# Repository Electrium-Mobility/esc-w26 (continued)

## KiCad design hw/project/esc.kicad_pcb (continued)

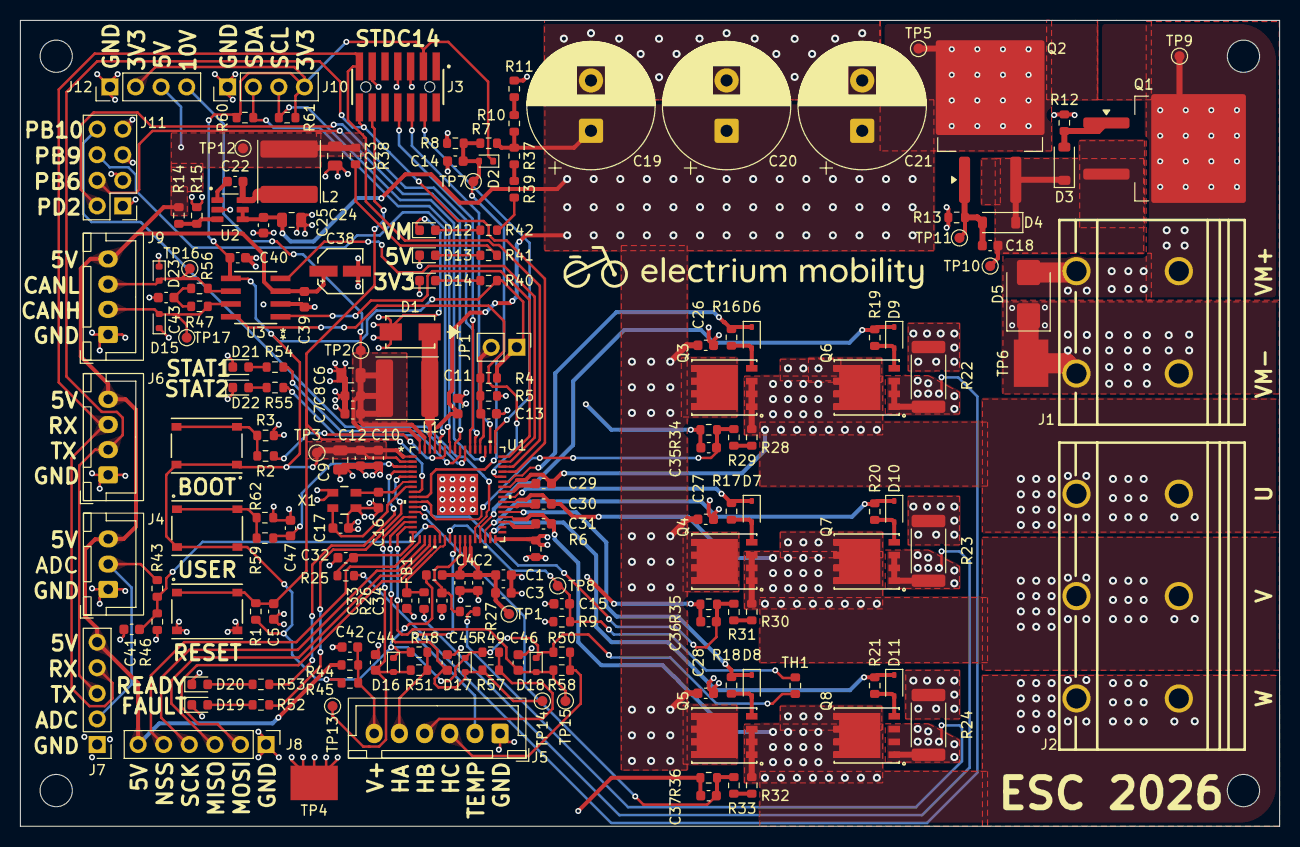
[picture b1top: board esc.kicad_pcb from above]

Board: 4 copper layers, 125.0 x 80.0 mm, 185 parts (0 on the bottom side), 101 nets.

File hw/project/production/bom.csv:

Designator,Footprint,Quantity,Value,LCSC Part #
"C1, C29, C3, C30, C31",0603,5,1uF/50V,C15849
"C10, C12, C14, C15, C2, C22, C25, C39, C4, C40, C41, C42, C47, C5, C7, C8",0603,16,0.1uF,C15725
"C11, C18, C26, C27, C28",0603,5,0.22uF/100V,C2169715
"C13, C32, C33, C34, C43, C44, C45, C46",0603,8,1nF/100V,C113793
"C16, C17",0603,2,8pF,C519117
"C19, C20, C21",CP_Radial_D12.5mm_P5.00mm,3,470uF/80V,C385881
C23,0805,1,22uF/25V,C45783
C24,0805,1,2.2uF/100V,C2981733
"C35, C36, C37",0603,3,470pF/100V,C326973
C38,EEEFKC220UAR,1,22uF/10V,C401733
"C6, C9",0805,2,10uF/50V,C440198
D1,SMA_STM,1,STPS1H100A,C165701
"D10, D11, D6, D7, D8, D9",D_SOD-323,6,BAT48JFILM,C2798199
"D12, D13, D14, D20",0603,4,2Vf_G,C125098
"D15, D23",D_SOD-523,2,5Vwm,C51912417
"D16, D17, D18, D2",D_SOD-523,4,BAT30KFILM,C2926449
D19,0603,1,2Vf_R,C94869
"D21, D22",0603,2,2Vf_A,C5730905
"D3, D4",D_SOD-123,2,12Vz,C699126
D5,D_SMB,1,36.8Vwm,C468909
FB1,0603,1,600@100MHz,C304319
J1,KFA-1016-10_16-2P,1,KFA-1016-10_16-2P,C475110
J10,PinHeader_1x04_P2.54mm_Vertical,1,I2C,C3329732
J11,PinHeader_2x04_P2.54mm_Vertical,1,Misc,C3333874
J12,PinHeader_1x04_P2.54mm_Vertical,1,Voltage Monitor,C3329732
J2,KFA-1016-10_16-3P,1,KFA-1016-10_16-3P,C475111
J3,SAMTEC_FTSH-107-01-L-DV-K-A,1,FTSH-107-01-L-DV-K-A,C5563894
J4,JST_XH_B3B-XH-A_1x03_P2.50mm_Vertical,1,Throttle,C144394
J5,JST_XH_B6B-XH-A_1x06_P2.50mm_Vertical,1,Hall,C144397
J6,JST_XH_B4B-XH-A_1x04_P2.50mm_Vertical,1,Serial,C144395
J7,PinHeader_1x05_P2.54mm_Vertical,1,2.54 Comm,C3347212
J8,PinHeader_1x06_P2.54mm_Vertical,1,SPI,C5427040
J9,JST_XH_B4B-XH-A_1x04_P2.50mm_Vertical,1,CAN,C144395
JP1,PinHeader_1x02_P2.54mm_Vertical,1,DIS_VDSMON,C5426960
L1,L_Sunlord_SWPA6045S,1,18uH,C96954
L2,L_Sunlord_SWPA6045S,1,33uH,C83451
"Q1, Q2",TO-263-2,2,SUM110P06-08L-E3,C5364638
"Q3, Q4, Q5, Q6, Q7, Q8",MOSFET_10N10F7_STM,6,STL110N10F7,C672185
"R1, R2, R3, R43, R46, R48, R49, R5, R50, R51, R57, R58, R59, R62",0603,14,10k,C25804
"R10, R11, R15, R28, R29, R30, R31, R32, R33, R4",0603,10,22.1k,C25961
"R12, R13, R14, R7",0603,4,118k,C25806
"R16, R17, R18, R19, R20, R21, R25, R26, R27",0603,9,10,C22859
"R22, R23, R24",2512,3,1m/3W,C53280154
"R34, R35, R36, R37, R39, R42, R60, R61",0603,8,2.2k,C4190
"R38, R40, R41, R52, R53, R54, R55",0603,7,150,C22808
"R47, R56",0603,2,60.4,C23090
"R6, R44",0603,2,0,C21189
"R8, R9",0603,2,4.7k,C23162
SW1,TS-1187A-B-A-B,1,BOOT0,C318884
SW2,TS-1187A-B-A-B,1,RESET,C318884
SW3,TS-1187A-B-A-B,1,USER,C318884
TH1,0603,1,10k/1%,C440252
TP4,KEYSTONE_5016,1,GND,C238129
TP6,KEYSTONE_5016,1,PGND,C238129
U1,QFN_IN32G4_STM,1,STSPIN32G4,C7434864
U2,LMR51610XDBVR-SOT95P280X145-6N,1,LMR51610XDBVR,C20539658
U3,SOIC8_4P9X3P9MC_MCH,1,ATA6561-GAQW-N,C616016
X1,xtal4_CX3225SB_AVX,1,SWXC5ACVF0-32.000000,C22399832

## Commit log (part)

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2026-01-30 Set up KiCad project with blank hierarchical sheets!
2026-01-30 Set up codebase. Not STM32CubeIDE yet though (when PCB v1 almost done)
2026-01-31 Add template files for Doxygen-style documentation
2026-01-31 Ready to add blank files (I fink)
2026-01-31 Update simulation docs
2026-02-01 Establish some motor/esc config stuff and create first set of functions to implement
2026-02-01 Add contribution steps
2026-02-08 Added esc Setters (throttle_cmd & motor_state) to Public Function Definitions
2026-02-08 Added esc Getters (Faulted, Flags, Inverter) to Public Function Definitions
2026-02-08 Forgot to Save
2026-02-09 Motor Interface / Config - Con/Deconstructors
    ESC initialization, ESC reset, ESC config validity + added preprocessor macros to esc.h subject to change
2026-02-13 Resolving Pull Request Issues
2026-02-13 Feedback Updates
    Improved code readability & removed hardcoding
2026-02-14 added control loop base
2026-02-19 Addressed Styling Choices and added Throttle Max/Min definitions.
2026-02-19 Updating return esc_get_fault_flags types and formatting
2026-02-19 Updated return for esc_is_faulted to != ESC_FAULT_NONE
2026-02-21 buck converter rev_1
2026-02-23 Configuring Control & Output Helpers
    Programmed _esc_update_setpoint, _esc_check_limits, _esc_update_output. Added preprocessor macro MAX_RPM
2026-03-01 Made requested changes
    Added preprocessor macros for deadband values, and fixed blaring fault flag manipulation issues
2026-03-03 fixed minor formatting
2026-03-03 Added Feedback and Commutation Helpers
2026-03-04 Set up Drive schem
2026-03-10 Update sym-lib-table
2026-03-10 fixed according to the comments
2026-03-11 Addressing minor things in PR
2026-03-17 Done with Drive stage EXCEPT analog sensing
2026-03-17 Added STM to Control sheet and proj libs
2026-03-17 Re-organized proj libs
2026-03-18 Cleaned up symbols and added footprint/3d model
2026-03-19 Create hal/ (previously platform/) header files
2026-03-19 Ready to assign hal/ tasks
2026-03-19 Minor edits to KiCad files
2026-03-22 Adding Main MATLAB files to Repo
2026-03-23 Renames & implementation for timing.c adc.c
2026-03-25 Rename timing -> time & cleanup
2026-03-25 pwm.c implementation
    needs revision but mostly complete
2026-03-30 resolving changes
2026-03-30 Pull main in
2026-03-31 Function definitions in host_test_utils.h & pwm.c implementation
2026-03-31 Removed misunderstanding
2026-03-31 input protection schematic and simulations added
2026-03-31 schematic updated
2026-04-01 added the notes as images
2026-04-02 rev_1:Application Circuitry
2026-04-11 host_test_utils.c implementation
2026-06-02 Adjusted notes in schem
2026-06-02 Refactor esc.c
2026-06-02 Further refactor of esc.c
2026-06-05 Adding to base model to sims folder
2026-06-10 Added gpio.c adn fault.c files to hal host
2026-06-13 Bob the builder!
2026-06-13 Fix host state utils bug
2026-06-13 Update docs for building
2026-06-13 Split up commutation method and feedback mechanism
2026-06-13 Clean up docs
2026-06-14 Adding base model to sims folder (#13)
    * Refactor esc.c
    * Further refactor of esc.c
    * Adding to base model to sims folder
    ---------
2026-06-14 Added gpio.c adn fault.c files to hal host (#14)
    * Refactor esc.c
    * Further refactor of esc.c
    * Added gpio.c adn fault.c files to hal host
    ---------
2026-06-14 filled out STSPIN32G4 for application circuitry
2026-06-17 analog sensing
    3 possible options for opamps, bootstrap caps depend on mosfets, so i gave the formula for that in the kicad.
2026-06-23 Revise Arnav's sensing task--changes to be made
2026-06-24 Upgrade to Kicad 10!
2026-06-25 Replace drive sheet with latest
2026-06-26 Updated local/hierarchical labels, renamed signals, and added alternate pin functions. Still need to review application circuit values fr.
2026-06-26 Add alternate pin functions from application circuitry
2026-06-28 Revise application circuitry
2026-06-28 Clean up control sheet (no boxes yet)
2026-06-29 Organize control sheet!
2026-06-29 Add note about EPAD
2026-06-29 Add creds to control sheet
2026-06-29 changed bucks, added ldo and new power chip
2026-06-29 Update phase labels and organize half bridges
2026-06-29 removed chip
2026-06-29 first power stage schematic revision
2026-06-29 power stage schematic done
2026-06-30 Add new library symbols and footprints
2026-06-30 fixed resistor values
2026-06-30 Update notes on half bridges and researched OPAMP PGA mode for current sense
2026-06-30 Create new hierarchical pins for OPAMPx
2026-06-30 cleaned up power stage schematic
